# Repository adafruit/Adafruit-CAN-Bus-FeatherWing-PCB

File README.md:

## Adafruit CAN Bus FeatherWing - MCP2515 PCB

<a href="http://www.adafruit.com/products/5709"><br/>
Click here to purchase one from the Adafruit shop</a>

PCB files for the Adafruit CAN Bus FeatherWing - MCP2515. 

Format is EagleCAD schematic and board layout
* https://www.adafruit.com/product/5709

### Description

CAN Bus is a small-scale networking standard, originally designed for cars and, yes, busses, but is now used for many robotics or sensor networks that need better range and addressing than I2C, and don't have the pins or computational ability to talk on Ethernet. CAN is 2 wire differential, which means it's good for long distances and noisy environments.

Messages are sent at about 1Mbps rate - you set the frequency for the bus and then all 'joiners' must match it, and have an address before the packet so that each node can listen in to messages just for it. New nodes can be attached easily because they just need to connect to the two data lines anywhere in the shared net. Each CAN devices sends messages whenever it wants, and thanks to some clever data encoding, can detect if there's a message collision and retransmit later. 

If you'd like to connect your Feather to a CAN Bus, the Adafruit CAN Bus FeatherWing with MCP2515 controller and TJA1051/3 transceiver will work with any and all Feathers! The controller used is the MCP2515, an extremely popular and well-supported chipset that has drivers in Arduino and CircuitPython and only requires an SPI port and two pins for chip-select and IRQ. Use it to send and receive messages in either standard or extended format at up to 1 Mbps.

We've added a few nice extras to this Feather to make it useful in many common CAN scenarios:

* 5V charge-pump voltage generator, so even though you are running 3.3V on a Feather board, it will generate a nice clean 5V as required by the transciever.
* 3.5mm terminal block that can be soldered in to get quick access to the High and Low data lines as well as a ground pin.
* 120 ohm termination resistor on board, you can remove the termination easily by cutting the jumper marked TERM on the top of the board.
* A spot that one can solder an optional (not included!) edge-launch DE-9 connector that is commonly used for connecting to CAN devices. L is connected to pin 2 and H is connected to pin 7. You could then plug this into an ODB-II cable to connect to a car's CAN network - you'll still need software to decode the messages though!
* Pre-connected CS and INT pins on the two pins to the left of the I2C Feather port - usually these are pins #5 and #6 but some feathers may have different numbering! You can cut the bottom solder jumpers and use the breakout pads to connect to any two IO pins you like.

Each order comes with an assembled 'Wing, terminal block and header. You will need to solder in the header yourself but its a quick task.

### License

Adafruit invests time and resources providing this open source design, please support Adafruit and open-source hardware by purchasing products from [Adafruit](https://www.adafruit.com)!

Designed by Limor Fried/Ladyada for Adafruit Industries.

Creative Commons Attribution/Share-Alike, all text above must be included in any redistribution. 
See license.txt for additional details.

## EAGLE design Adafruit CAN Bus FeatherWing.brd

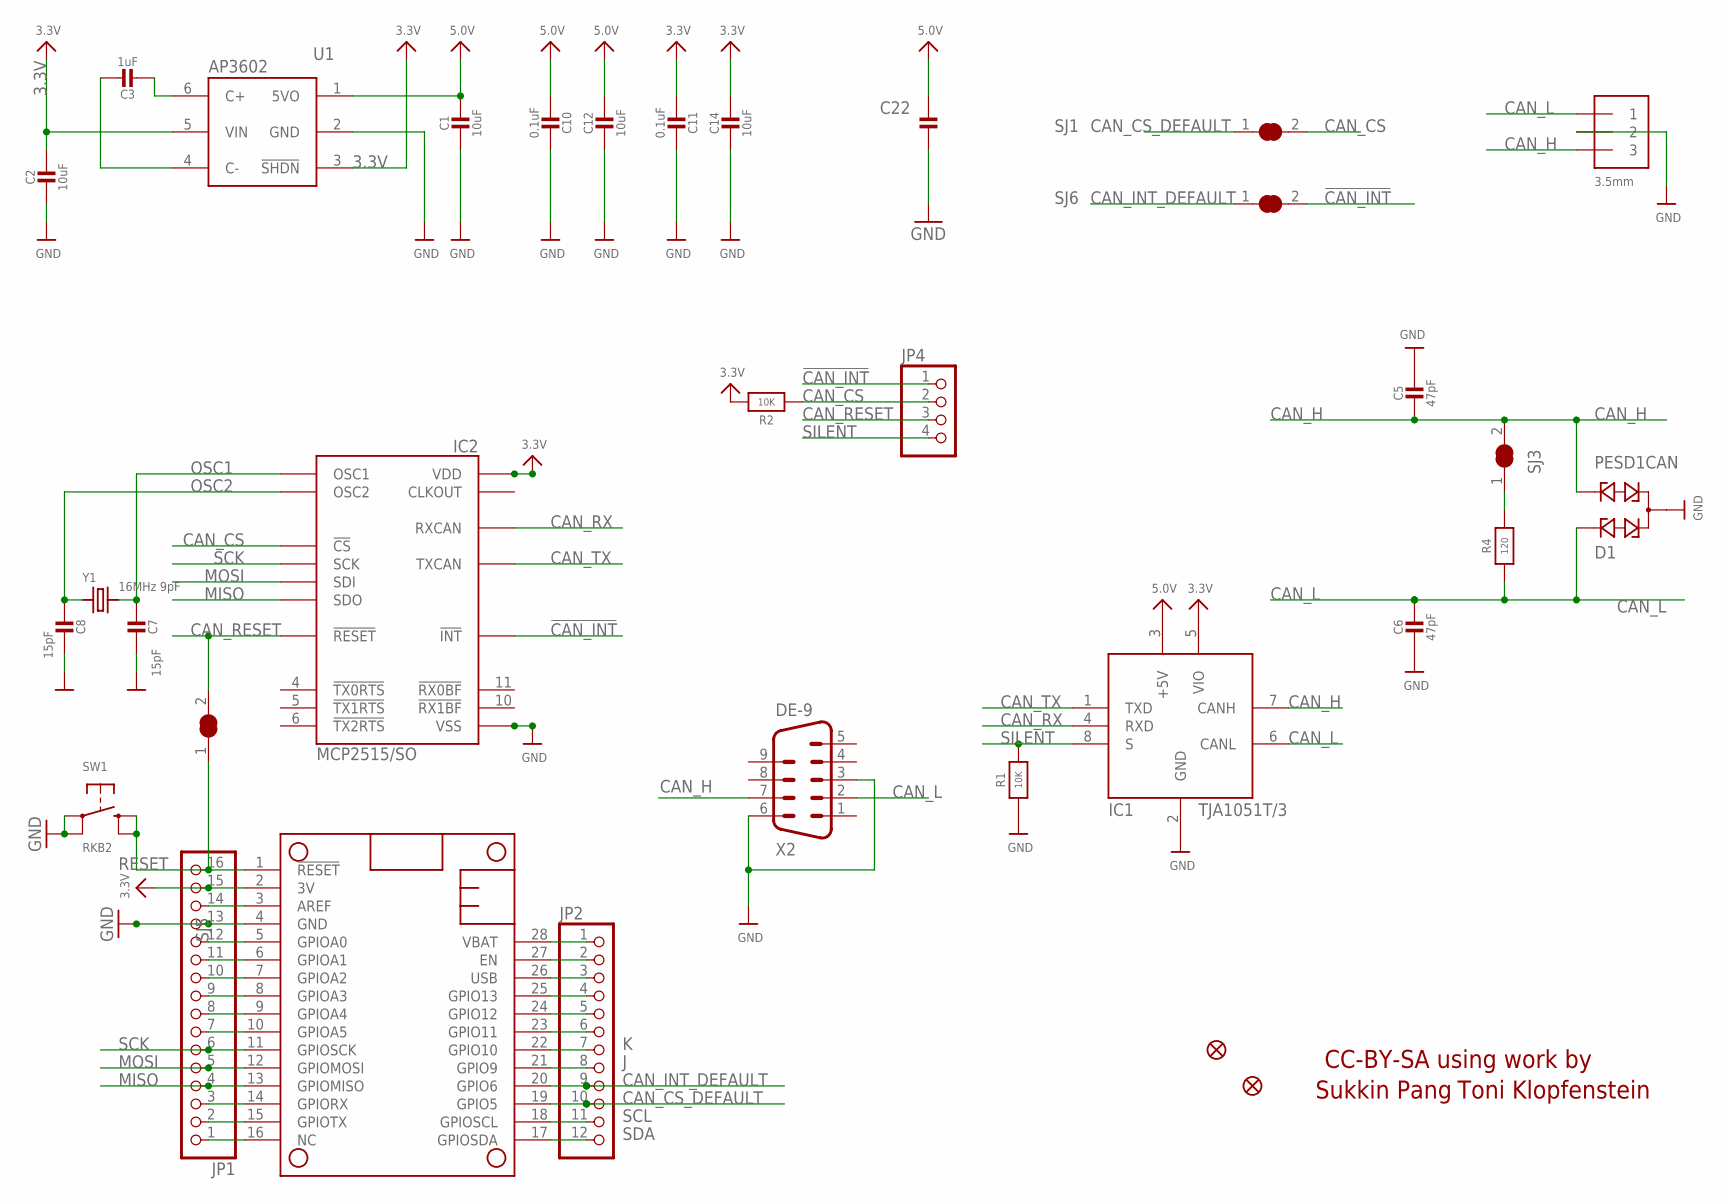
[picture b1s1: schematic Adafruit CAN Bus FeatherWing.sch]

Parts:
C1, C2, C12, C14: 10uF; 0805-NO
C3: 1uF; 0805-NO
C5, C6: 47pF; 0603-NO
C7, C8: 15pF; 0603-NO
C10, C11, C22: 0.1uF; 0603-NO
D1: PESD1CAN; SOT23
FID2, FID3: FIDUCIAL_1MM
IC1: TJA1051T/3; SOIC8_150MIL
IC2: MCP2515/SO; SOIC18WIDE
JP1: HEADER-1X16ROUND; 1X16_ROUND
JP2: HEADER-1X12; 1X12_ROUND
JP4: HEADER-1X4ROUND; 1X04_ROUND
MS1: FEATHERWING_NODIM
NEOPIX1: 3.5mm; TERMBLOCK_1X3-3.5MM
R1, R2: 10K; 0603-NO
R4: 120; 0603-NO
SJ1, SJ3, SJ5, SJ6: SOLDERJUMPER_CLOSED; SOLDERJUMPER_CLOSEDWIRE
SW1: RKB2; BTN_RKB2_4.6X2.8
U1: AP3602; SOT23-6
X2: DE-9; M09D
Y1: 16MHz 9pF; CRYSTAL_3.2X2.5

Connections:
3.3V: C2.1, C11.2, C14.1, IC1.5 (VIO), IC2.18 (VDD), JP1.15, MS1.2 (3V), R2.2, U1.3 (!SHDN), U1.5 (VIN)
5.0V: C1.1, C10.2, C12.1, C22.2, IC1.3 (+5V), U1.1 (5VO)
!CAN_INT: IC2.12 (!INT), JP4.1, SJ6.2
A: JP1.12, MS1.5 (GPIOA0)
AREF: JP1.14, MS1.3 (AREF)
B: JP1.11, MS1.6 (GPIOA1)
C: JP1.10, MS1.7 (GPIOA2)
CAN_CS: IC2.16 (!CS), JP4.2, R2.1, SJ1.2
CAN_CS_DEFAULT: JP2.10, MS1.19 (GPIO5), SJ1.1
CAN_H: C5.2, D1.2, IC1.7 (CANH), NEOPIX1.3, SJ3.2, X2.7
CAN_INT_DEFAULT: JP2.9, MS1.20 (GPIO6), SJ6.1
CAN_L: C6.1, D1.1, IC1.6 (CANL), NEOPIX1.1, R4.1, X2.2
CAN_RESET: IC2.17 (!RESET), JP4.3, SJ5.2
CAN_RX: IC1.4 (RXD), IC2.2 (RXCAN)
CAN_TX: IC1.1 (TXD), IC2.1 (TXCAN)
D: JP1.9, MS1.8 (GPIOA3)
E: JP1.8, MS1.9 (GPIOA4)
EN: JP2.2, MS1.27 (EN)
F: JP1.7, MS1.10 (GPIOA5)
G: JP1.1, MS1.16 (NC)
GND: C1.2, C2.2, C5.1, C6.2, C7.1, C8.1, C10.1, C11.1, C12.2, C14.2, C22.1, D1.3, IC1.2 (GND), IC2.9 (VSS), JP1.13, MS1.4 (GND), NEOPIX1.2, R1.1, SW1.A, SW1.A' (P1), U1.2 (GND), X2.3, X2.6
J: JP2.8, MS1.21 (GPIO9)
K: JP2.7, MS1.22 (GPIO10)
L: JP2.6, MS1.23 (GPIO11)
M: JP2.5, MS1.24 (GPIO12)
MISO: IC2.15 (SDO), JP1.4, MS1.13 (GPIOMISO)
MOSI: IC2.14 (SDI), JP1.5, MS1.12 (GPIOMOSI)
N: JP2.4, MS1.25 (GPIO13)
unnamed: C3.2, U1.6 (C+)
unnamed: C3.1, U1.4 (C-)
unnamed: R4.2, SJ3.1
OSC1: C7.2, IC2.8 (OSC1), Y1.2
OSC2: C8.2, IC2.7 (OSC2), Y1.1
RESET: JP1.16, MS1.1 (!RESET), SJ5.1, SW1.B (S), SW1.B' (S1)
RX: JP1.3, MS1.14 (GPIORX)
SCK: IC2.13 (SCK), JP1.6, MS1.11 (GPIOSCK)
SCL: JP2.11, MS1.18 (GPIOSCL)
SDA: JP2.12, MS1.17 (GPIOSDA)
SILENT: IC1.8 (S), JP4.4, R1.2
TX: JP1.2, MS1.15 (GPIOTX)
USB: JP2.3, MS1.26 (USB)
VBAT: JP2.1, MS1.28 (VBAT)

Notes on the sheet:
Toni Klopfenstein
Sukkin Pang
CC-BY-SA using work by

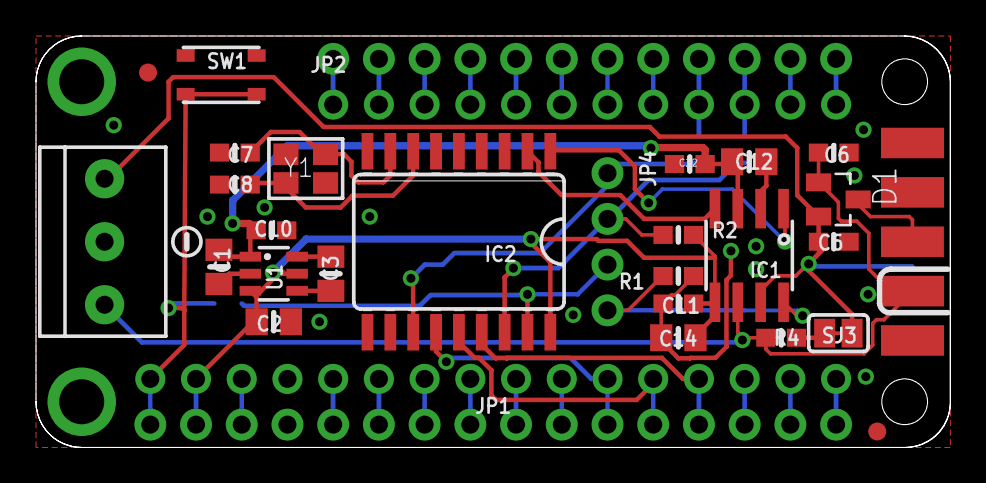
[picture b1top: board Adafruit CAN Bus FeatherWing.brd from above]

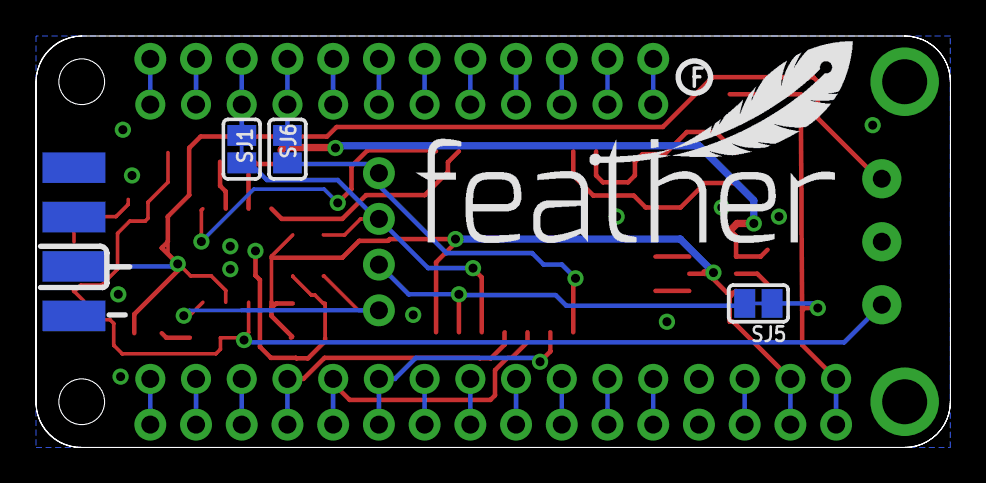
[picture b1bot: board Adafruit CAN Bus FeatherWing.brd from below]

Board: 2 copper layers, 50.8 x 22.9 mm, 52 parts (12 on the bottom side), 42 nets.

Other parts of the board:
PLABEL0: PLABEL0
PLABEL1: PLABEL1
PLABEL2: PLABEL2
PLABEL3: PLABEL3
PLABEL4: PLABEL4
PLABEL5: PLABEL5
PLABEL6: PLABEL6
PLABEL8: PLABEL8
PLABEL9: PLABEL9
PLABEL10: PLABEL10
PLABEL11: PLABEL11
PLABEL12: PLABEL12
PLABEL13: PLABEL13
PLABEL14: PLABEL14
PLABEL15: PLABEL15
PLABEL16: PLABEL16
U$21: SYMBOL_MINUS
U$22: FEATHERLOGO
U$33: PCBFEAT-REV-040

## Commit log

2023-03-22 adding cookiecutter output

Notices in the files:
parts and their libraries:
microbuilder: This work is placed in the public domain, and may be freely used for commercial and non-commercial work with the following conditions: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
SparkFun-Aesthetics: Licensing: CC v3.0 Share-Alike You are welcome to use this library for commercial purposes.
